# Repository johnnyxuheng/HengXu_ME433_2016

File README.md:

{\rtf1\ansi\ansicpg1252\cocoartf1404\cocoasubrtf110
{\fonttbl\f0\fswiss\fcharset0 Helvetica;}
{\colortbl;\red255\green255\blue255;}
\margl1440\margr1440\vieww10800\viewh8400\viewkind0
\pard\tx720\tx1440\tx2160\tx2880\tx3600\tx4320\tx5040\tx5760\tx6480\tx7200\tx7920\tx8640\pardirnatural\partightenfactor0

\f0\fs24 \cf0 Heng Xu @ Apr/04/2016}

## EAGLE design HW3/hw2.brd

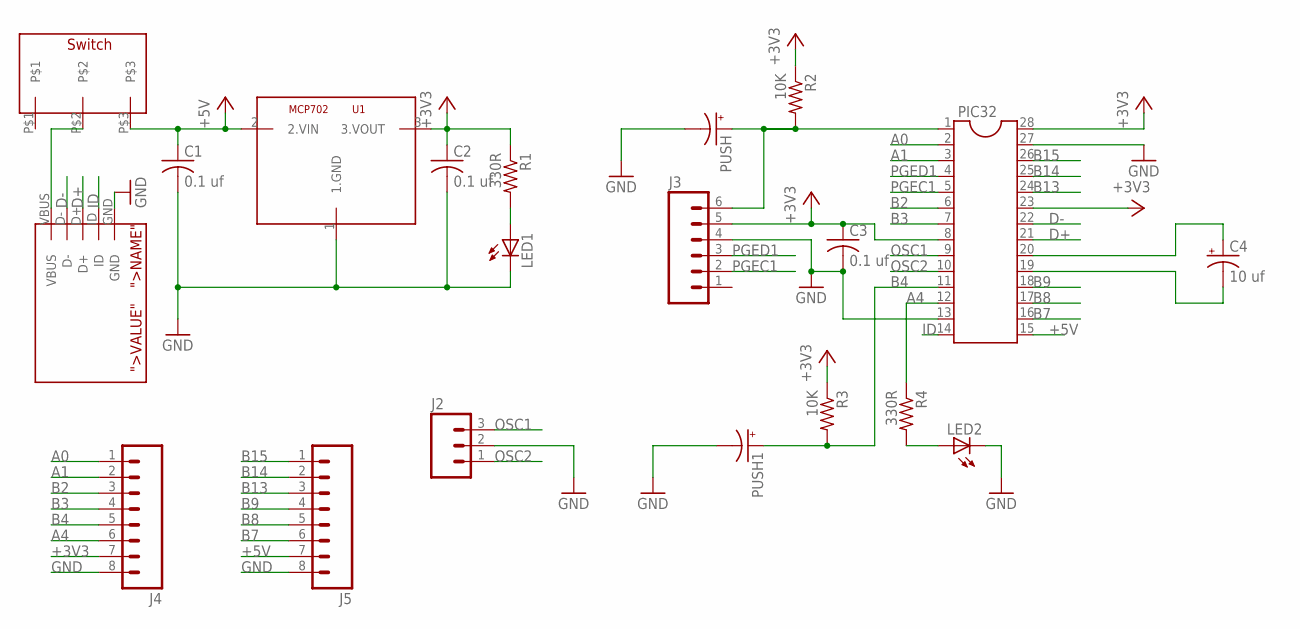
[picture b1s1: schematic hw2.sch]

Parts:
C1, C2, C3: 0.1 uf; C025-024X044
C4: 10 uf; TT2D4
J2: M03LOCK; 1X03_LOCK
J3: M06NO_SILK_YES_STOP; 1X06_NO_SILK_YES_STOP
J4, J5: M08NO_SILK; 1X08_PIN1_NO_SILK
LED1, LED2: LED3MM
PIC32: DIL28-3
PUSH, PUSH1: CPOL-USTAP5-60; TAP5-60
R1, R4: 330R; 0204/7
R2, R3: 10K; 0204/7
U$1: SWITCH
U$2: MCP1702; TO92
U$3: USBNEW; USB-MB-H

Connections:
+3V3: C2.1, C3.1, J3.5 (VDD), J4.7, PIC32.8, PIC32.23, PIC32.28, R1.1, R2.1, R3.1, U$2.3 (3.VOUT)
+5V: C1.1, J5.7, PIC32.15, U$1.P$3, U$2.2 (2.VIN)
A0: J4.1, PIC32.2
A1: J4.2, PIC32.3
A4: J4.6, PIC32.12, R4.1
B2: J4.3, PIC32.6
B3: J4.4, PIC32.7
B4: J4.5, PIC32.11, PUSH1.+, R3.2
B7: J5.6, PIC32.16
B8: J5.5, PIC32.17
B9: J5.4, PIC32.18
B13: J5.3, PIC32.24
B14: J5.2, PIC32.25
B15: J5.1, PIC32.26
D+: PIC32.21, U$3.D+
D-: PIC32.22, U$3.D-
GND: C1.2, C2.2, C3.2, J2.2, J3.4 (VSS), J4.8, J5.8, LED1.K (C), LED2.K (C), PIC32.13, PIC32.27, PUSH.-, PUSH1.-, U$2.1 (1.GND), U$3.GND
ID: PIC32.14, U$3.ID
unnamed: U$1.P$2, U$3.VBUS
unnamed: LED1.A, R1.2
unnamed: J3.6 (MCLB), PIC32.1, PUSH.+, R2.2
unnamed: LED2.A, R4.2
unnamed: C4.+, PIC32.20
unnamed: C4.-, PIC32.19
OSC1: J2.3, PIC32.9
OSC2: J2.1, PIC32.10
PGEC1: J3.2 (PGC), PIC32.5
PGED1: J3.3 (PGD), PIC32.4

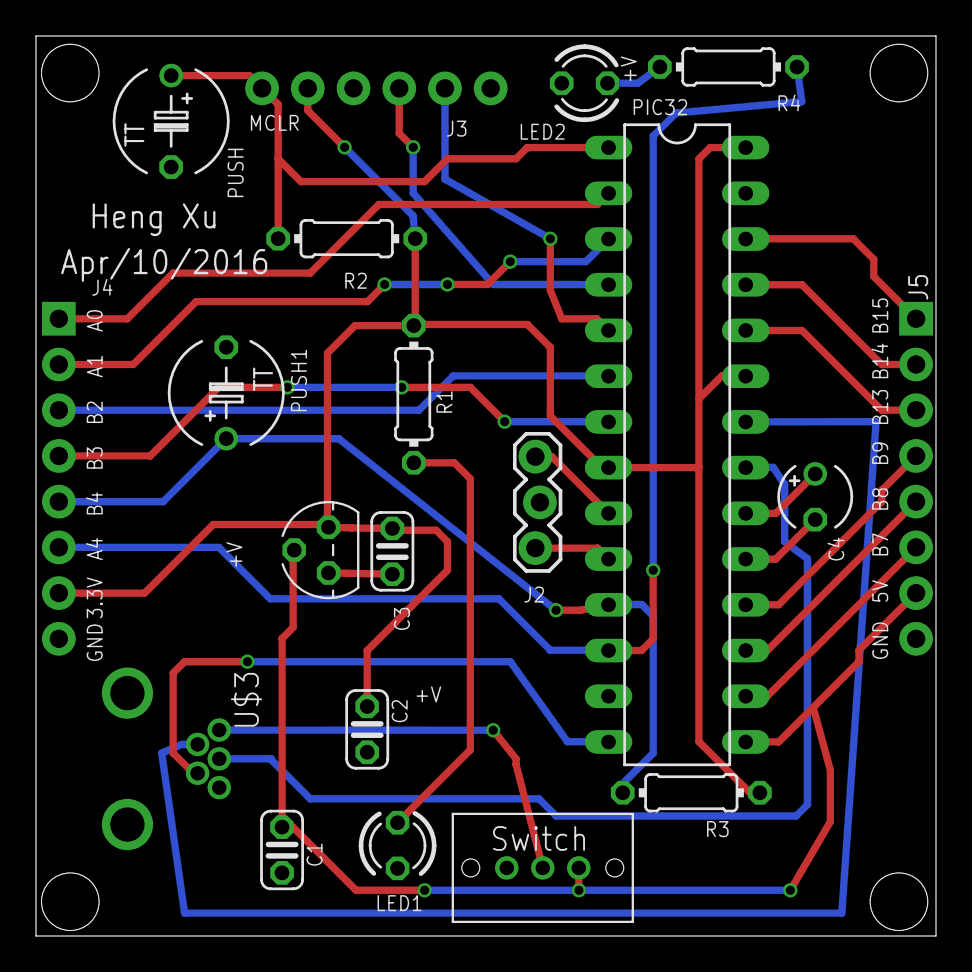
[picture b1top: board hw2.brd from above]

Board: 2 copper layers, 50.0 x 50.0 mm, 20 parts (0 on the bottom side), 28 nets.

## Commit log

2016-04-04 My first commit
2016-04-04 delete
2016-04-04 test
2016-04-04 Revert "test"
    This reverts commit 8c65259a05902e19517fc0f6d0ef392bf3c3661f.
2016-04-04 test1
2016-04-04 change1
2016-04-04 Correct the understanding of questions
2016-04-04 Correct my understanding of questions
2016-04-14 HW3
    Ready to be checked before order
2016-04-18 HW4_1
2016-04-19 HW4_2
2016-04-21 HW4 final
2016-04-26 HW4_updata
2016-04-26 HW6_final
2016-04-26 HW6_Update
2016-05-08 HW5_Draw_1337
2016-05-08 HW5_IMU
2016-05-23 HW11
2016-06-08 Final
